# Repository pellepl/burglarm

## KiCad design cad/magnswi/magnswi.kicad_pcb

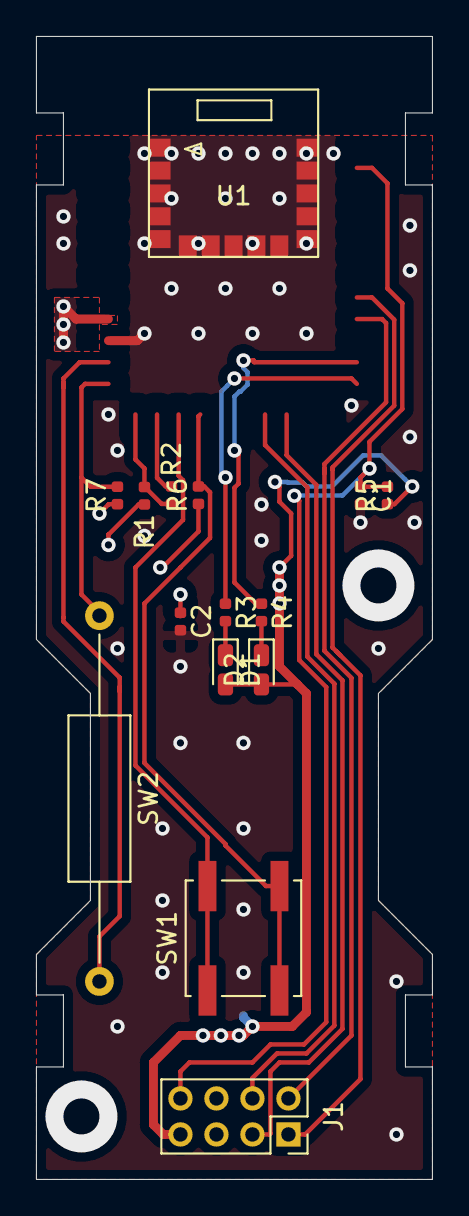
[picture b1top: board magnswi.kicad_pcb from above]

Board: 2 copper layers, 22.0 x 63.5 mm, 16 parts (1 on the bottom side), 8 nets.

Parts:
BT1: Battery_Cell; BatteryHolder_MPD_BC2003_1x2032
C1: 0.1uF; C_0402_1005Metric
C2: 4.7uF; C_0402_1005Metric
D1, D2: LED; LED_0603_1608Metric_Castellated
J1: Conn_02x04_Top_Bottom; PinSocket_2x04_P2.00mm_Vertical
R1, R2: 5k; R_0402_1005Metric
R3: 240; R_0402_1005Metric
R4: 300; R_0402_1005Metric
R5: 10k; R_0402_1005Metric
R6, R7: 100k; R_0402_1005Metric
SW1: SW_DPST_x2; SW_Push_1P1T_NO_CK_KSC6xxJ
SW2: SW_Reed; R_Axial_DIN0309_L9.0mm_D3.2mm_P20.32mm_Horizontal
U1: nrf52832_mod_holyiot17095; holyiot17095

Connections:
+3V0: BT1.1, C2.1, D1.2, D2.2, J1.7, R1.2, R5.1, R6.1, R7.1
BATT_SPL: R1.1, R2.2
GND: BT1.2, C1.2, C2.2, J1.6
unnamed: D1.1, R3.2
unnamed: D2.1, R4.2
RESET: C1.1, J1.8, R5.2
SW_MAGNET: R7.2, SW2.1
SW_TAMPER: R6.2, SW1.1

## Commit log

2021-10-28 initial
2021-11-06 darn aliexpress
